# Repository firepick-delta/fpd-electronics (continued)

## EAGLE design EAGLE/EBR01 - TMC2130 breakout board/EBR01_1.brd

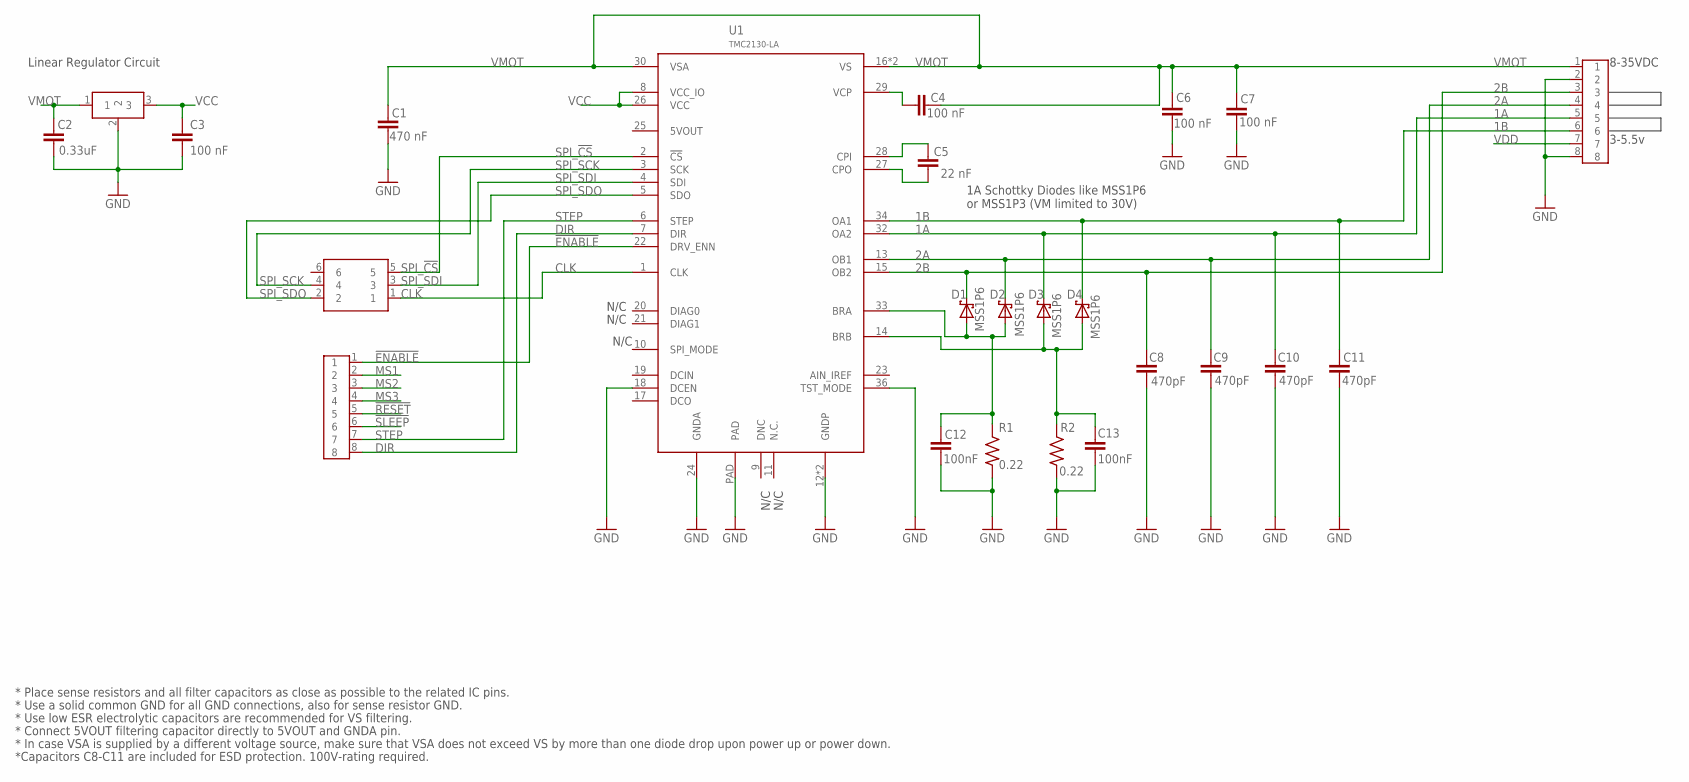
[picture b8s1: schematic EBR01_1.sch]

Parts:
C1: 470 nF; C0603
C2: 0.33uF; C0603
C3, C4, C6, C7: 100 nF; C0603
C5: 22 nF; C0603
C8, C9, C10, C11: 470pF; C0603
C12, C13: 100nF; C0603
D1, D2, D3, D4: MSS1P6; MICRO-SMP
J1, J2: CPL-CON-HEADER-0.1IN-8P-M; CON-HDR-8POS-MALE
J3: CPL-CON-HEADER-0.1IN-2X3P-M; CON-HDR-2X3P
Q1: CPL-REG-LIN-5V-0.1A; SOT-89
R1, R2: 0.22; R1206
U1: TMC2130-LA; QFN36-(5X6)

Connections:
1A: C10.1, D3.NEG (C), J2.5, U1.32 (OA2)
1B: C11.1, D4.NEG (C), J2.6, U1.34 (OA1)
2A: C9.1, D2.NEG (C), J2.4, U1.13 (OB1)
2B: C8.1, D1.NEG (C), J2.3, U1.15 (OB2)
!ENABLE!: J1.1, U1.22 (DRV_ENN)
!RESET!: J1.5
!SLEEP!: J1.6
BRA: C12.1, D1.POS (A), D2.POS (A), R1.2, U1.33 (BRA)
BRB: C13.1, D3.POS (A), D4.POS (A), R2.2, U1.14 (BRB)
CLK: J3.1, U1.1 (CLK)
CPI: C5.2, U1.28 (CPI)
CPO: C5.1, U1.27 (CPO)
DIR: J1.8, U1.7 (DIR)
GND: C1.1, C2.1, C3.1, C6.2, C7.2, C8.2, C9.2, C10.2, C11.2, C12.2, C13.2, J2.2, J2.8, Q1.2, R1.1, R2.1, U1.12 (GNDP), U1.18 (DCEN), U1.24 (GNDA), U1.35 (GNDP), U1.36 (TST_MODE), U1.PAD
MS1: J1.2
MS2: J1.3
MS3: J1.4
SPI_!CS!: J3.5, U1.2 (!CS)
SPI_SCK: J3.4, U1.3 (SCK)
SPI_SDI: J3.3, U1.4 (SDI)
SPI_SDO: J3.2, U1.5 (SDO)
STEP: J1.7, U1.6 (STEP)
VCC: C3.2, Q1.3, U1.8 (VCC_IO), U1.26 (VCC)
VCP: C4.1, U1.29 (VCP)
VDD: J2.7
VMOT: C1.2, C2.2, C4.2, C6.1, C7.1, J2.1, Q1.1, U1.16 (VS), U1.30 (VSA), U1.31 (VS)

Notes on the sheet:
3-5.5v
8-35VDC
N/C
* Place sense resistors and all filter capacitors as close as possible to the related IC pins.
* Use a solid common GND for all GND connections, also for sense resistor GND.
* Use low ESR electrolytic capacitors are recommended for VS filtering.
* Connect 5VOUT filtering capacitor directly to 5VOUT and GNDA pin.
* In case VSA is supplied by a different voltage source, make sure that VSA does not exceed VS by more than one diode drop upon power up or power down.
1A Schottky Diodes like MSS1P6 or MSS1P3 (VM limited to 30V)
Linear Regulator Circuit
*Capacitors C8-C11 are included for ESD protection. 100V-rating required.

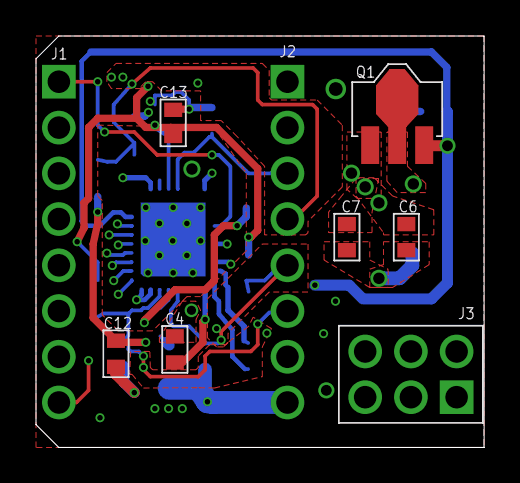
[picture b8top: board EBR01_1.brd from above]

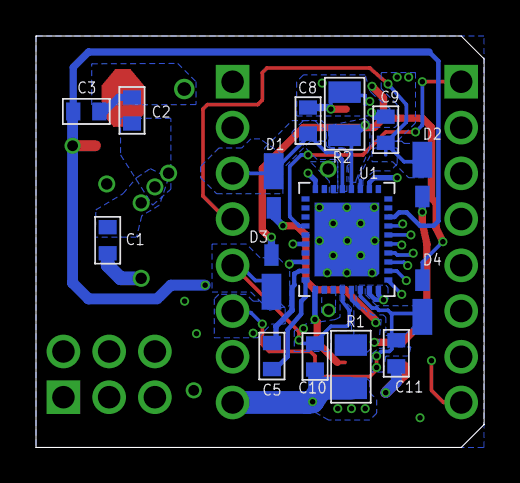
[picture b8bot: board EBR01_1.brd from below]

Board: 4 copper layers, 24.9 x 22.9 mm, 24 parts (15 on the bottom side), 20 nets.

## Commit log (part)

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2015-08-05 New library
2015-08-06 Connected device CPL-MDR-2PHSTEPPER (Trinamic TMC2130), and Introduced SMT footprint 0603
2015-08-06 Copied over symbols and devices from other repos
2015-08-06 Copied over logos for Tinwhiskers library
2015-08-07 Created Device for SDRAM and imported all packages from FPD-temp library
2015-08-07 Created devices for the STM429 microchip and the L3GD20 gyroscope
2015-08-10 Added devices needed to TMC2130 stepper motor board (C5, C6, C9)
2015-08-10 Completed all devices for various capacitors on Trinamics motion board.
2015-08-10 Completed more devices for Trinamic driver PCB. Polar capacitors and voltage suppressor diode included.
2015-08-11 Completed several more components for TMC2130
2015-08-12 Initial schematic capture of EBR01
2015-08-12 Completed current-sense resistors, made some corrections to pvs packages.
2015-08-12 Completed 10 new resistors for the TMC2130, a 3-pin header, and an SOT-23 diode.
2015-08-14 Have begun replacing placeholder components with TWT Library components. Cleaning up schematic in preparation for layout.
2015-08-14 Updated footprints, cleaned up some of the dimensions which were on the wrong layer (tPlace). They're now on tDocu so they don't show up on the board.
2015-08-16 Updated library to include the last several parts needed for EBR01 breakout board.
2015-08-16 Updated all components to reflect accurate devices. Smashed most of the parts that required it. The only remaining issues with the schematic are the external voltage regulator and a couple unconnecte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
2015-08-18 Schematic tentative finalized.
2015-08-18 Added parts necessary for ECAM01 board
2015-08-18 New test board for FPD accuracy testing
2015-08-18 Fixed a symbol for a header
2015-08-18 Added incomplete schematic capture for ECAM01 board
2015-08-19 Corrected connections on the RAM and the DCMI connectors, as well as the oscillator and the J1 Connector. Added TP1-TP2, and added a bus for the RAM connections to decrease clutter.
2015-08-19 Acquired some necessary devices for completing ECAM01 board
2015-08-22 Breakout board layout
2015-08-23 Version 1 of ETEST01, these were the production files sent to fab, received 8/23/2015
2015-08-24 Routing done.
2015-08-24 Added rev with bus for RAM, simplifies schematic.
2015-08-24 Adding library parts for EBR01, updating schematic
2015-08-24 Schematic updates, added parts to library for EBR01
2015-08-25 Added all necessary library parts for Ethernet circuit, USART1, USART2. Finished schematic capture of Ethernet circuit, USART1, USART2.
2015-08-26 DXF's of ECAM schematics
2015-08-26 Trace widths for motor lines increased to handle 2A current. Eliminated/approved all DRC errors except those for Q1, which remain for review by Neil. Refined DRC check to reflect manufacturing specs 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
2015-08-26 Add fiducial (was copied from FirePick library, but added a >NAME on the symbol)
2015-08-26 Add >NAME to package TDOCU layer
2015-08-26 Made a row of fiducials because i didn't want to lay out 779 of them by hand
2015-08-27 Created DRC folder to store relevant DRC checks
2015-08-27 Attempted to remove air wires. Flipped R2 to eliminate vias on sense line. Re-routed wires on ground plane and power plane.
2015-08-27 Added parts to library for USB_OTG connection.
2015-08-27 Added USB connection to ECAM01 board, relevant devices.
2015-08-27 Corrected all (118) DRC errors for EBR01 board. Thickened traces for R2 GND connection, added extra vias to improve grounding, rerouted N$3 trace running directly under GND pad so more vias could be 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
2015-08-27 Added vias to R1 GND connection, made all traces to GND wider. Moved board up so that Y=0 lines up with the bottom of the board and fixed Y dimension to reflect true height. Overall cleanup of vias a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
2015-08-28 Fixed error: line 13607: invalid value '' for attribute 'name' in tag <net>
2015-08-28 Created parts for EMC03, began schematic for EMC03. Symbol for NXP microchip in preliminary format.
2015-08-31 Added parts for USB, MicroSD, and SWD connections, imported all into schematic for EMC03 board, named and labeled all relevant connections.
2015-09-01 Tweaked routing and placement on board. This is the version that will be submitted to the board house. Exported GERBERs and checked them in.
2015-09-01 just kidding, this is the final version. Added a chamfer to one of the corners that might interfere on the Y axis
2015-09-01 Added RS-485 chip, connected ethernet, SD, USB to processor. Connected power net to processor.
2015-09-02 Updated schematic to include UART0, UART1, MicroSD, SWD, RS-485.
2015-09-03 Fixed connections for RS-485, added resistors for fail-safe mode and termination. Created RJ-45 device for RS-485 connection. Added LED device and placed on schematic 7 LEDs (4 green, 3 red). Created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
2015-09-03 Schematic has been updated to assist with sourcing, cleaned up Refdes'.
2015-09-07 Began integration into EMC02 legacy schematic. Unnecessary components removed from EMC02. MCU, peripherals added to the EMC02 schematic. Schematic renamed EMC03-Motion Control. LEDs added, switching 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
2015-09-07 Clock for +60 Demo
2015-09-08 FInal version of clock PCB before sending to board house
2015-09-08 fixing, checked into wrong dir
2015-09-08 ZIP as sent to board house
2015-09-08 Added two pushbuttons and a connector for the horn
2015-09-08 Got call from board house, forgot solder mask in GERBER ZIP. Updating ZIP with aforementioned soldermask layers.
2015-09-08 Updated corners a bit, in order to squeeze in a few more fiducials. Exported to GERBER. Sent to board house.
2015-09-09 Integrated motor drivers into the EMC03 schematic, E-checked the EBR01 board with the netlist. Began similarifying things cromulently.
2015-09-11 Integrated the MCU into the EMC02 schematic. The EMC03 schematic is accompanied by a BOM and pinout for the LPC1768. The pinout does not yet reflect the changes of 9/11/15, but all the major connecti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
2015-09-14 Adding BOM generation script (bom-ex.ulp) and partsdb.txt that was used for the boards using in the beta test production run.
2015-09-14 Added a BOM for EMC03, created a checklist for PCB mfr, finalized schematic (rearranged refdes', fixed missing values, etc.)
2015-09-14 Modified the BOM to reflect connector, resonator changes. All component parts for EBR01 and their equivalents on EMC03 were ordered and the BOMs were updated to reflect this. The database for the new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
2015-09-15 Updated BOM, Database, Schematic for final parts
2015-09-15 Fixing whitespace issues in partsdb.txt so that BOM generator doesn't freak out
2015-09-15 documentation pdfs
2015-09-15 EMC03: Updated schematic, BOM, database, and parts library to include all revisions. This includes schematic capture for interfaces (endstops, motors, encoders, RS-485 interface, modular tools 1 and 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
2015-09-16 Resized EMC03 board, 50mm per side. All connector 3D models have been imported for design in Cubify. Database has been updated to include E-stop connector (corrected). Connectors have been added to b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
2015-09-18 Arranged EMC03 board as much as possible. Updated PCB Checklist with testpoint data. Updated test points to pads, as per schematic instructions.
2015-09-28 Updated schematic to integrate Intel Edison into EMC03 (USB chip for serial console, USB hub for all peripherals and associated EEPROM, second RS-485 transceiver for Edison). USB-B connection has bee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
2015-09-30 Updated schematic to incorporate tweaks proposed by Neil. Generated new and complete BOM, updated parts database.
2015-10-03 Created preliminary final schematic for ECA03
2015-10-04 Component placement begun
2015-10-04 Preliminary placement and routing done for EFD01. Preliminary placement done for EMC03. All schematics are ready for review (A0 for ECAM03 needs to be defined, also SS for EFD01, ECAM03, etc.)
2015-10-05 Split the EMC03 into EMC03 and EFP01 (front panel board) to make routing 10000000x easier
2015-10-05 Finalized schematics (minus potential LDO regulator) for all boards. Layout partially done for EFD01
2015-10-05 Replaced switching regulator with a smaller LDO, with smaller accompanying components. Preliminary component placement for EMC03. Partial routing of power nets.
2015-10-06 All parts placed for EMC03, X Axis routed.
2015-10-06 Routed EFD01, ECAM03 boards. Modification needs to be made for hole/keepout in ECAM03. EMC03 X and Y sides routed. Will need to increase some trace widths.
2015-10-06 Routing completed for EMC03, need to clean DRC, format. Routing completed for ECAM03.
2015-10-07 Routed all boards. EFP01 has a serious problem with spacing. Even on minimum allowable there are 300 DRC errors.
2015-10-09 Completed boards. Please look at airwires connecting thermal pads to GND vias. They shouldn't be present due to the vias.
2015-10-11 Adding a library with Tin Whiskers logo
2015-10-11 Updated all boards to include changes for production
2015-10-11 Added +3V3 line for LCD, DXF for Will
2015-10-11 Updated motor hole size to 7mm Dia. Rerouted around.
2015-10-11 Updated DXF for 7mm motor hole
2015-10-11 Made an LED board for the end effector 2.0. It is intended to be mounted above the 5MP ELP USB camera, and driven by the AP3032 LED controller that is on the ECAM02 board.
2015-10-12 Added a ring light for the up-looking camera board
2015-10-12 On the two ring light boards, I changed the LEDs from 1206 package to 1210 in order to accomodate a brighter LED.
2015-10-12 Added frames, logos, part numbers, and fiducials
2015-10-12 Replaced fiducials with newer fiducials that have keepouts / restrict layers
2015-10-12 Final(??) Versions of FPD boards.
2015-10-12 Things
2015-10-12 Created BOM for EMC03
2015-10-12 Created BOM for EFP01
2015-10-12 no message
2015-10-12 Re-jiggered switching power supply for LED controller. Re-routed and whatnot. Generated GERBERs for REV--
2015-10-12 Re-jiggered switching power for LED controller, rerouted and whatnot. Added trace for WS2812B. Swapped DAC wire (A0 was going to the LED driver instead of analog out). Generated GERBERs for Rev--.
2015-10-12 Added a 1206 10 ohm resistor (1/4W)
2015-10-12 Beefed up a few trace widths (~0.1524mm to 0.5mm) in key areas that will have high amounts of current passing through them. This will generate a merge conflict with Dan's last push, I will attempt a 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
2015-10-12 Made some simple adjustments (moved traces, increased width on current carrying components). Added P/N and TW logo. Generated gerbers for Rev--.
2015-10-12 Minor changes to EFP01. One show-stopper DRC error (overlapping traces). Added logo and P/N. Other misc. tweaks. Generated Gerbers for Rev--.
2015-10-12 Generated GERBERs for Rev--
2015-10-12 Added gerbers for Rev--
2015-10-13 BOMs complete for all FPD boards
2015-10-15 BOMs finished, inventory sheet created.
2015-10-16 Added 7-Pin Connectors, highlighted changes in blue
2015-10-16 Sorted BOMs by ref des. Changed qty on PHR-7
2015-10-16 Added qty 2 B7B-PH-SM4-TB(LF)(SN)
2015-10-16 Created Cable Assembly BOM.
2015-10-16 Created ESOL01 Schematic and Board. Added parts to DB, added parts to inventory.
2015-10-17 Changing resistor tolerances to 1%
2015-10-17 Tweaks to boards, mostly moving silkscreen reference designators and TDOCU/BDOCU stuff. In a few cases, the reference designators for bottom parts were on the TDOCU layer instead of the BDOCU layer. 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
2015-10-17 Added trestrict layers on three mounting holes
2015-10-18 Routed ESOL01, created MTHOLE(M3) part for future use
2015-10-18 Fixed ESOL01 for mechanical restrictions
2015-10-19 DXF'ed ESOL01, Updated Inventory/Order Form, Cable Assy BOM completed
2015-10-19 Fixed BOM, began adding DFM changes
2015-10-19 Added decoupling caps to EFD01, ECAM02, rearranged parts for better fit, increased power trace width, updated BOM and database.
2015-10-20 Made REV 2 modifications, including increasing width of power traces, adding vias to power traces, and addition of LEDs to all modular tools. Catch diodes added to ESOL01 board to prevent coils from 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
2015-10-21 Routing for differential pairs included in EFP01. Minor changes to BOM, inventory list.
2015-10-21 Resistance check, minor changes to EFP01 BOM (100 Ohm changed to 120 Ohm)
2015-10-22 No changes except re-DXF'd ESOL01
